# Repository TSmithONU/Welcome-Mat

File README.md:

# Welcome-Mat
Board files and software for WOSU Welcome Mat

The WOSU Welcome Mat consists of 7 lamps with WOSU logos. The goal of this project was to rebuild and update the previous hardware. To do this, used a Teensy 3.2, VS1053 breakout from Adafruit, and a LiDar sensor.
The LiDar sensor is calibrated to set threshold. When that threshold is crossed, it triggers playback of an audio file. The program contains a command set for use on the serial port. This allows the user to run diagnostic commands.
These include recalibration, scanning the SD card, taking a LiDar reading, and more. This repository contains the custom PCB files, as well as the teensy software.

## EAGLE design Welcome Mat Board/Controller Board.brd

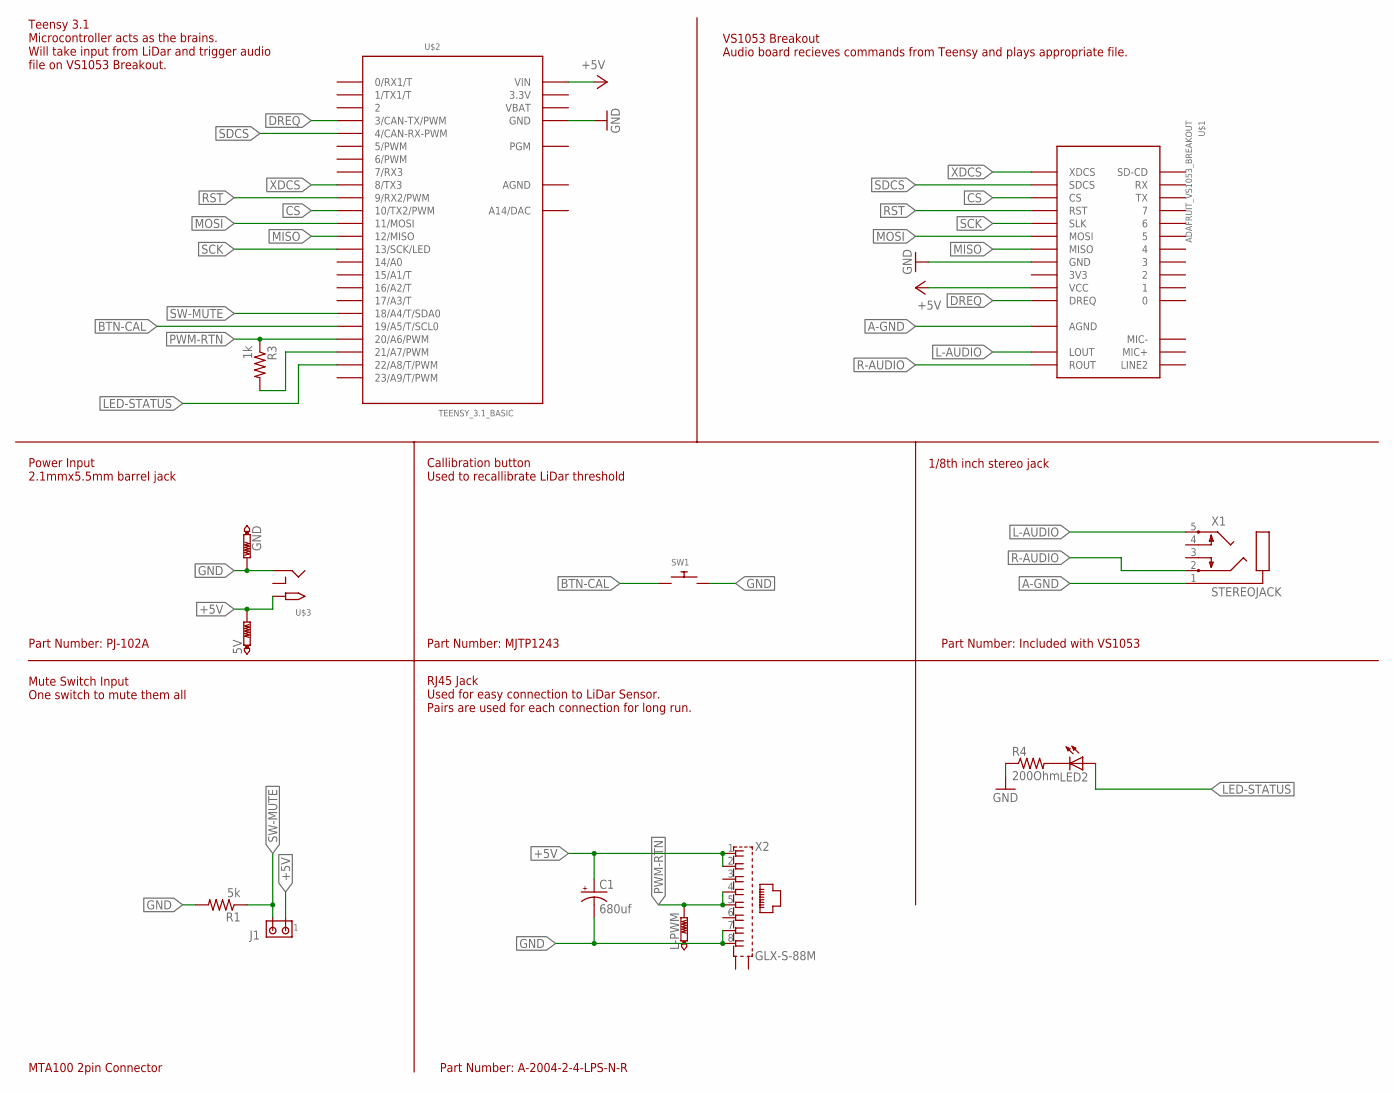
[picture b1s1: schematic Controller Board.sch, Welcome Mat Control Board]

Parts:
5V: PTR1PAD1-13; P1-13
C1: 680uf; E5-10,5
GND: PTR1PAD1-13; P1-13
J1: MTA02-100; 10X02MTA
L-PWM: PTR1PAD1-13; P1-13
LED2: LED3MM
R1: 5k; 0204/7
R3: 1k; 0204/5
R4: 200Ohm; 0204/7
SW1: SWITCH_PUSHBUTTONEVQ-PE; TACT_PANA-EVQ
U$1: ADAFRUIT_VS1053_BREAKOUT
U$2: TEENSY_3.1_BASIC
U$3: 2.1MMJACKTHM; PJ-102A
X1: STEREOJACK; STX3100
X2: GLX-S-88M

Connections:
3.3V: U$2.3.3V, U$2.3.3V1 (3.3V)
+5V: 5V.TP, C1.+, J1.1, U$1.P$10 (VCC), U$2.VIN, U$3.TIP, X2.1, X2.2
A-GND: U$1.P$13 (AGND), U$1.P$14 (AGND), U$1.P$20 (AGND), X1.1
AGND: U$2.AGND
BTN-CAL: SW1.P$1, U$2.19/A5 (19/A5/T/SCL0)
CS: U$1.P$3 (CS), U$2.10 (10/TX2/PWM)
DREQ: U$1.P$11 (DREQ), U$2.3 (3/CAN-TX/PWM)
GND: C1.-, GND.TP, R1.2, R4.1, SW1.P$2, U$1.P$8 (GND), U$1.P$12 (GND), U$2.GND, U$2.GND1 (GND), U$3.RING, X2.7, X2.8
L-AUDIO: U$1.P$15 (LOUT), X1.5
LED-STATUS: LED2.A, U$2.22/A8 (22/A8/T/PWM)
MISO: U$1.P$7 (MISO), U$2.12 (12/MISO)
MOSI: U$1.P$6 (MOSI), U$2.11 (11/MOSI)
unnamed: R3.2, U$2.21/A7 (21/A7/PWM)
unnamed: LED2.K (C), R4.2
PWM-RTN: L-PWM.TP, R3.1, U$2.20/A6 (20/A6/PWM), X2.4, X2.5
R-AUDIO: U$1.P$16 (ROUT), X1.2
RST: U$1.P$4 (RST), U$2.9 (9/RX2/PWM)
SCK: U$1.P$5 (SLK), U$2.13 (13/SCK/LED)
SDCS: U$1.P$2 (SDCS), U$2.4 (4/CAN-RX-PWM)
SW-MUTE: J1.2, R1.1, U$2.18/A4 (18/A4/T/SDA0)
VBAT: U$2.VBAT
XDCS: U$1.P$1 (XDCS), U$2.8 (8/TX3)

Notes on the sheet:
Teensy 3.1 Microcontroller acts as the brains. Will take input from LiDar and trigger audio file on VS1053 Breakout.
VS1053 Breakout Audio board recieves commands from Teensy and plays appropriate file.
Power Input 2.1mmx5.5mm barrel jack
Callibration button Used to recallibrate LiDar threshold
1/8th inch stereo jack
Mute Switch Input One switch to mute them all
RJ45 Jack Used for easy connection to LiDar Sensor. Pairs are used for each connection for long run.
Part Number: PJ-102A
Part Number: MJTP1243
Part Number: Included with VS1053
MTA100 2pin Connector
Part Number: A-2004-2-4-LPS-N-R

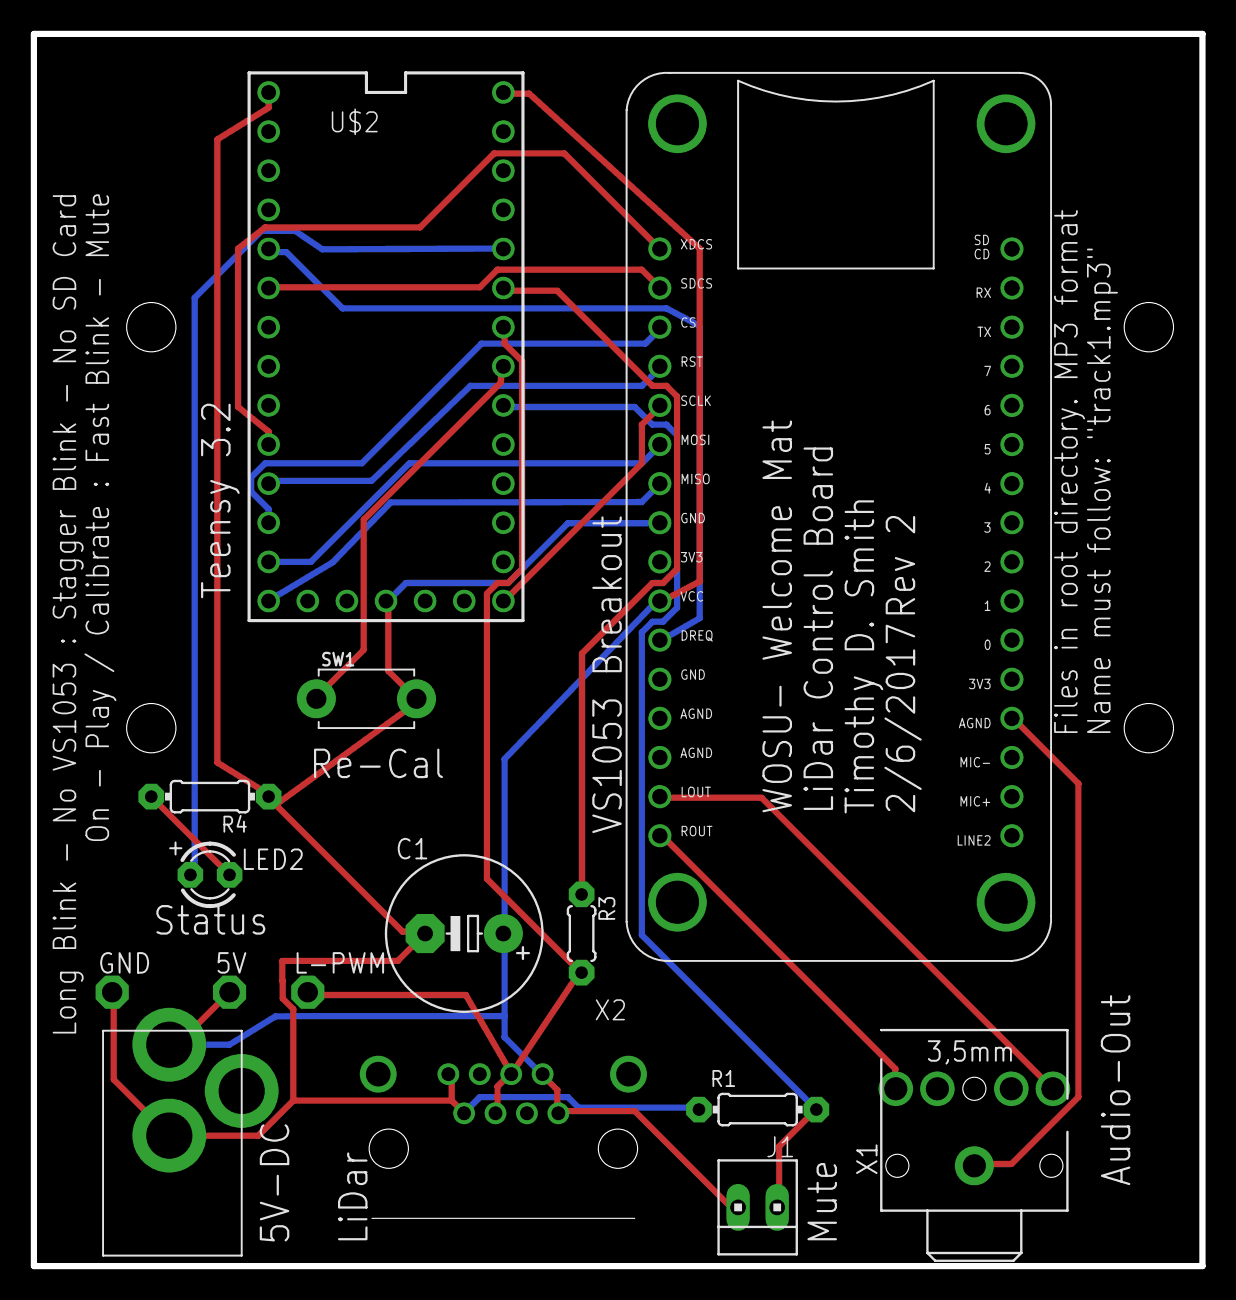
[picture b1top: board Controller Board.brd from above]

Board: 2 copper layers, 75.9 x 80.0 mm, 15 parts (0 on the bottom side), 20 nets.

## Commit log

2017-07-19 Initial Upload to GIT
